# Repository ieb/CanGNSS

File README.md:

# NMEA2000 GNSS Receiver

A NMEA2000 device to provide rapid position and COG SOG update as well as other GNSS information including satelite data.

# PGN messages and rates.

* 129025L Position Rapid update 5Hz
* 129026L COG/SOG Rapid Update 2.5Hz
* 129029L Position data 1Hz
* 126992L System Time, 1Hz
* 129539L GNSS DOPs 1Hz
* 129540L GNSS Satellites in View 0.5Hz
* 127258L Magnetic Variation 1Hz

Magnetic variation is calculated every 60s from WMN2020 World model coefficients.

# Hardware

* Attiny3224 MCU
* UBlox M8N module pre configured at 19200 Baud with UBX messages.
* MCP 2515 CAN driver with TJ1050 Transceiver

# Code

Starts up, establishes CAN connectivity then reads UBX messages as they are produced and transfers them directly onto the NMEA200 bus.  There is a monitoring UART that runs at 115200 which can be used to see log messages and reboot. Press h to get a menu. The WNM2020 model takes 63ms to calculate which is long enough for a standard 64 byte UART buffer to overflow. This code requires a patched megaTinyCode code base with a 256 byte UART buffer.

# Pins

                                ANT
      --------------------------------
      |          A B C D E           |
      | F                            |
      | G                            |
      | H                            |
      | I                            |
      |                     j k l m  |
      --------------------------------

* A +5v   
* B 0v
* C UDPI
* D RX Console
* E TX Console

* F 12V - CAN
* G 0V
* H CAN-L
* I CAN-H

* j 0v
* k TX Ublox
* l RX Ublox
* m 5v Ublox

# Settings.

The MCU can program the device to its standard settings. press h to get the menu on the console. For more advanced settings u-center or pyGPSClient can be used, but first the MCU Uart connected to the Ublox module must be disabled.

Press u to disable the Uart, then without turning the device off, connect to the Ubloc TX and RX pins. The Uart will be re-enabled on reboot or power cycle.

I have found pyGPSClient to be much easier than u-center as Windows tends to grab the comp ports and GPS stream making it
almost impossible to connect u-center. (tips welcome).  So I use pyGPSClient on a Ubuntu VM running in OSX. First connect with screen to get the console

    screen /dev/ttyUSB0 115200

pres h to get the menu and u to disconnect the UART. The Ctrl-a + k  to exit screen.

Then connect pyGPSClient to the ublox via a serial and reconfigure as required.

## Expected setup.

* Baud 19200
* UBX Messages only, no NMEA

The satelite setup blow gives about 1m 3D accuracy without SBAS corrections, and slightly less once the SBAS
corrections are received. Should probably write this into code.
* CFG-GNSS  also set in code
* msgVer 0, mumTrkChHw 32 (read only), mumTrkChUse 32, numConfigBlocks 7
* gnssId 0 (GPS), res 4, max 16, enable 1, mask 1 eg L1C/A 1,575.42MHz
* gnssId 1 (SBAS), res 2, max 4, enable 1, mask 1 eg L1C/A 1,575.42MHz
* gnssId 2 (Galileo), res 4, max 8, enable 1, mask 1 eg E1 1,575.42MHz
* gnssId 3 (BelDou) disabled 0,0,0,0
* gnssId 4 (IMESS) diabled 0,0,0,0
* gnssId 5 (QZSS) res 1, max 1, enable 1 mask 1, L1C/A  1,575.42MHz
* gnssId 6 (GLonas) res 2, max 5 enable 1, mask 1 L1
*
* CFG-ITMF,ection Jamming det enabled on active antena, all else defaults.
* CFG_NAV5 set modes to sea
* CFG-SBAS as default enable  1 (ignored), test 0, range 1, diffCorr 1, integrety 0, maxSBAS 3
* PRN 120, 123, 127-129, 133, 135-138

* Also set in code
* CFG_RATE Solution interval 200ms, measurement ratio 5, UTC. 
* NAV setup all off except
* NAV-DOP 6
* NAV-POSLLH 1
* NAV-PVT 5
* NAV-SAT 9
* NAV-VELNED 2

# PCB

The PCM is designed in KiCad (ancient version), and milled on a CNC miller. The attiny3224 is underneath the ublox module, which has a ground plane on the bottom layer.

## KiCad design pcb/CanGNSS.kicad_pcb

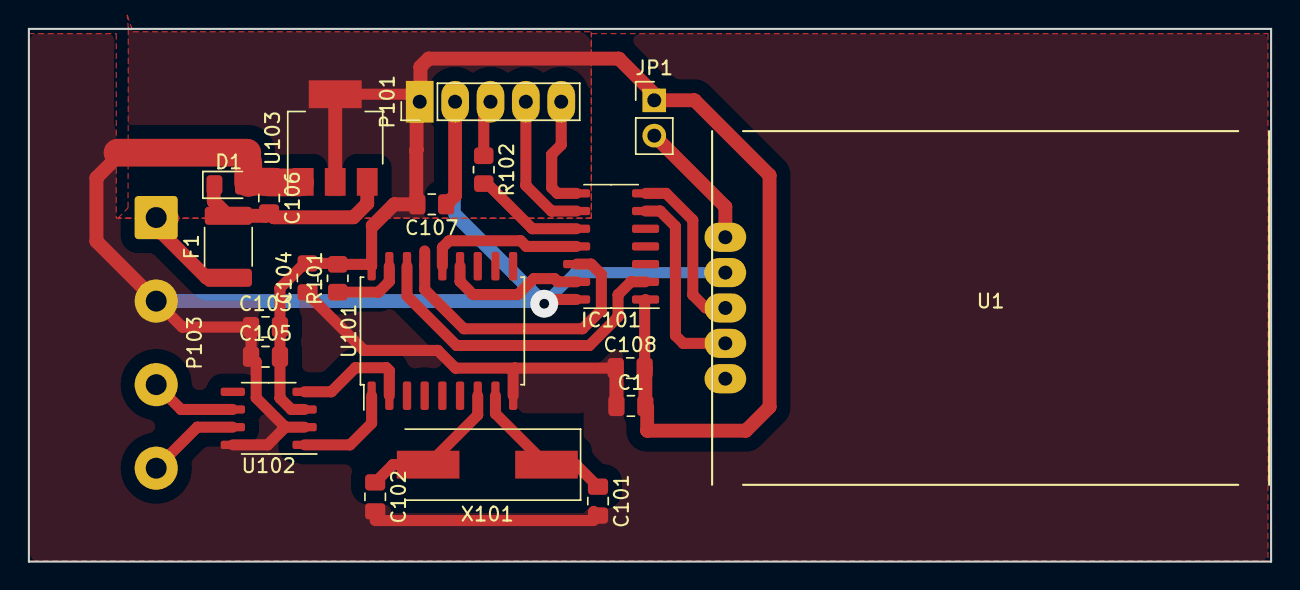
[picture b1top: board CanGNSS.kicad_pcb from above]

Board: 2 copper layers, 89.2 x 38.3 mm, 22 parts (0 on the bottom side), 22 nets.

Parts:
C1, C103, C106, C107: 10uF; C_0805_2012Metric_Pad1.18x1.45mm_HandSolder
C101, C102: 22pF; C_0805_2012Metric_Pad1.18x1.45mm_HandSolder
C104, C105, C108: 100nF; C_0805_2012Metric_Pad1.18x1.45mm_HandSolder
D1: D; D_0805_2012Metric_Pad1.15x1.40mm_HandSolder
F1: Polyfuse_Small; Fuse_1812_4532Metric_Pad1.30x3.40mm_HandSolder
IC101: ATTINY3224-SS; SO-14_3.9x8.65mm_P1.27mm
JP1: Jumper_2_Bridged; PinHeader_1x02_P2.54mm_Vertical
P101: Debug; PinHeader_1x05_P2.54mm_Vertical
P103: CAN; SolderWire-1.5sqmm_1x04_P6mm_D1.7mm_OD3mm
R101: 10K; R_0805_2012Metric_Pad1.20x1.40mm_HandSolder
R102: 470R; R_0805_2012Metric_Pad1.20x1.40mm_HandSolder
U1: neo-m8n-module-mini
U101: MCP2515; SOIC-18W_7.5x11.6mm_P1.27mm
U102: TJA1050; SO-8_3.9x4.9mm_P1.27mm
U103: NCP1117ST50T3G; SOT-223-3_TabPin2
X101: 16MHz; Crystal_SMD_HC49-SD

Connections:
5V: C1.2, C103.2, C104.2, C105.2, C107.2, C108.2, IC101.1 (VCC), JP1.1 (A), P101.1, R101.2, U101.18 (Vdd), U102.3 (Vcc), U103.2 (VO)
5Vswitched: JP1.2 (B), U1.5 (Vcc)
12v: F1.1, P103.1
CANCS: IC101.2 (PA4(AIN4/XDIR/SS)), U101.16 (CS)
CANH: P103.4, U102.7 (CanH)
CANL: P103.3, U102.6 (CanL)
DEBUG_RX: IC101.9 ((AIN11/SCL)PB0), P101.4
DEBUG_TX: IC101.8 ((AIN10/SDA)PB1), P101.5
GND: C1.1, C101.2, C102.2, C103.1, C104.1, C105.1, C106.1, C107.1, C108.1, D1.2 (A), IC101.14 (GND), P101.2, P103.2, U1.4 (Gnd), U101.9 (GND), U102.2 (GND), U102.8 (S), U103.1 (GND)
GPSRX: IC101.6 (PB3(RX0/TOSC1)), U1.2 (Rx)
GPSTX: IC101.7 (PB2(Tx0/TOSC2/EVOUTB)), U1.3 (Tx)
MISO: IC101.12 ((RX1/MISO/AIN2)PA2), U101.15 (SO)
MOSI: IC101.11 ((TX1/MOSI/AIN1)PA1), U101.14 (SI)
unnamed: C106.2, D1.1 (K), F1.2, U103.3 (VI)
unnamed: IC101.10 ((UDPI/RESET)_PA0), R102.2
unnamed: U101.2 (CANRX), U102.4 (RXD)
unnamed: U101.1 (CANTX), U102.1 (TXD)
unnamed: C101.1, U101.8 (OSC1), X101.1
unnamed: C102.1, U101.7 (OSC2), X101.2
unnamed: R101.1, U101.17 (RESET)
SCK: IC101.13 ((XCK/SCK/AIN3)PA3), U101.13 (SCK)
UDPI: P101.3, R102.1

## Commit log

2023-06-17 Added VELNED and started NMEA2000 messages
2023-06-24 ublox setup done, mostly working, nmea2000 not tested
2023-06-25 Added ability to configure at startup
2023-06-30 Added diagnostic output
2023-07-03 Working and tested version
2023-07-04 Cleaned up memory usage
2023-07-04 Added Readme
2023-07-04 photo
2023-07-05 Enabled reconfig in case the BBR fails
2023-07-06 Allow disconnect to use pyGPSClient
2023-07-06 Set Version number
2023-07-06 And print it out
2023-07-06 Updated doc, so I dont forget how to configure
2023-07-11 Fixed COG message and made satelites better
2023-07-16 Fixes to COG and SOG
2023-09-09 Fixed 49day overflows
2025-04-27 Updated board and config
